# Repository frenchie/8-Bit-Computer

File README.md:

# An 8-bit Computer

My take on breadboard computer designs from [Ben Eater](https://eater.net/8bit) ([YouTube](https://www.youtube.com/channel/UCS0N5baNlQWJCUrhCEo8WlA)) and [James Bates](https://github.com/jamesbates/jcpu) ([YouTube](https://www.youtube.com/channel/UCH09NwwJsfThwLKvc6kxl4Q)).

## Licensing

* The AVR Code for the 7-segment display driver, ALU & Clock are available to use under a MIT license
* The Microcode generator & associated tools are available to use under a MIT license
* All KiCAD design files are licensed Creative Commons Attribution-ShareAlike 4.0 International (CC BY-SA 4.0)
* The AVR In-System Programmer AVR includes Peter Fluery's i2c library and is licensed under the GPLv3
* The Included AVR Makefiles are Public Domain.

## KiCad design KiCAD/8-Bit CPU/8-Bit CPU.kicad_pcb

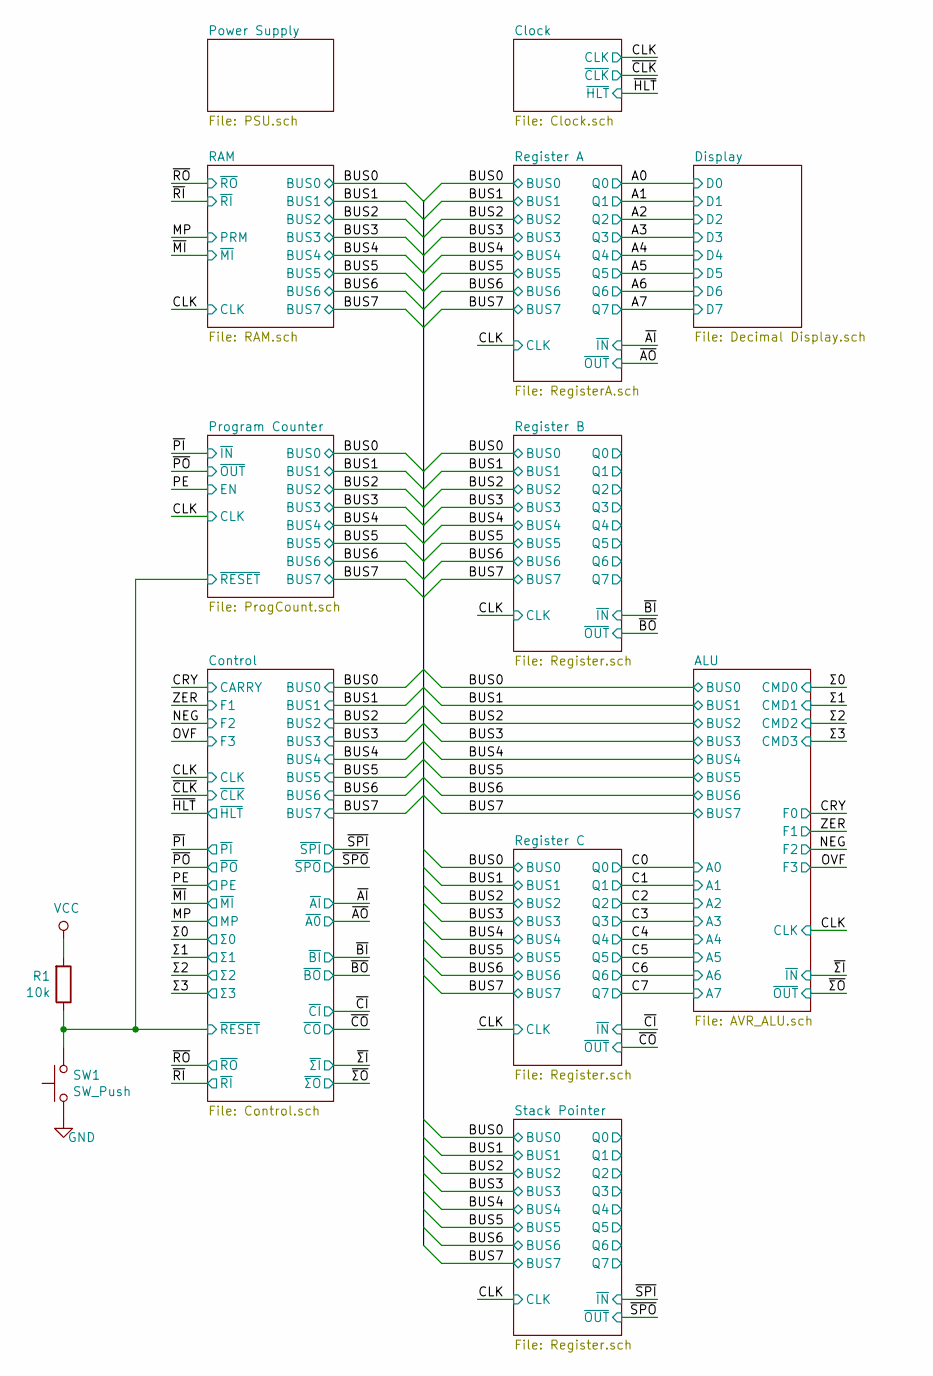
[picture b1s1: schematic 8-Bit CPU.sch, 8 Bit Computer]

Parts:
R1: 10k; R_0805_2012Metric
SW1: SW_Push; SW_TH_Tactile_Omron_B3F-10xx_Fixed

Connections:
/Control/~RESET: R1.1, SW1.2; also elsewhere on the board
GND: SW1.1; also elsewhere on the board
VCC: R1.2; also elsewhere on the board

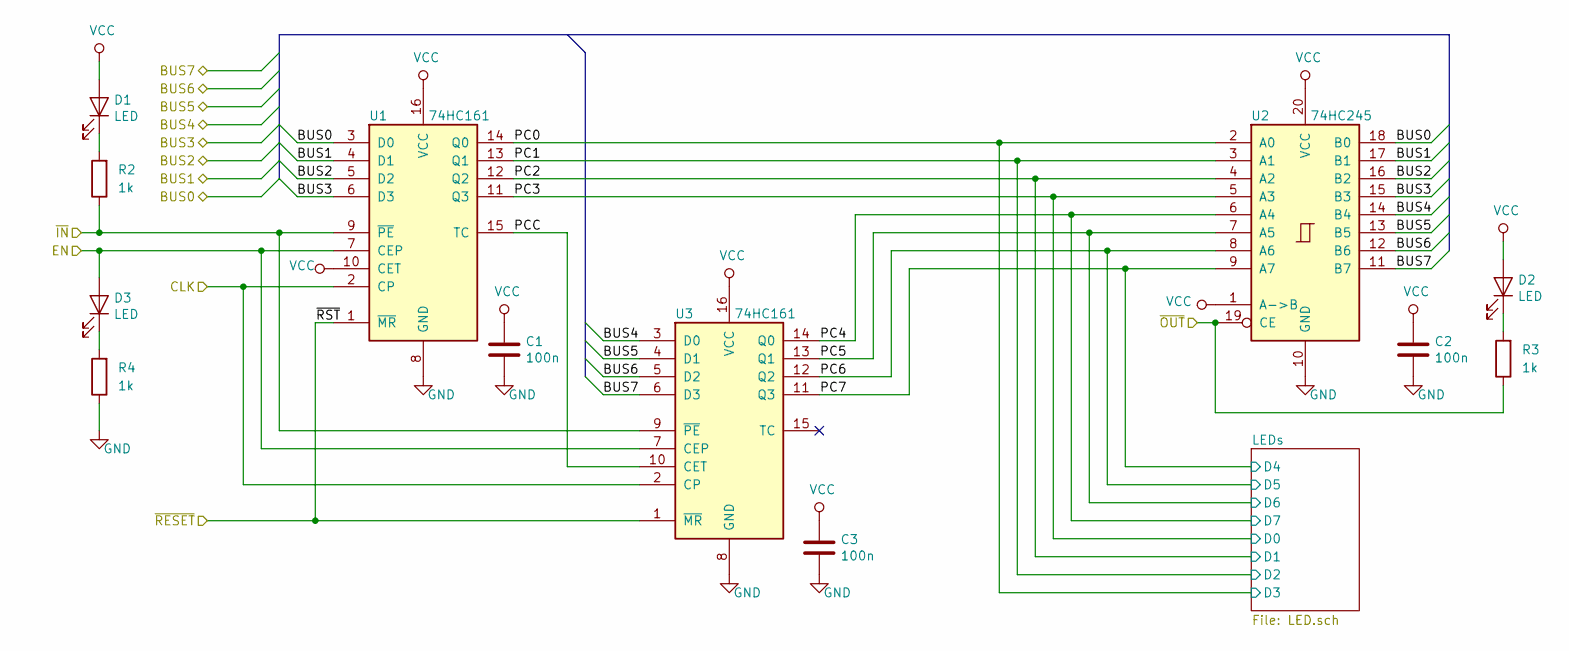
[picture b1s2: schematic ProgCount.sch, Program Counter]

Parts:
C1, C2, C3: 100n; C_0805_2012Metric
D1, D2, D3: LED; LED_0805_2012Metric
R2, R3, R4: 1k; R_0805_2012Metric
U1, U3: 74HC161; SOIC-16_3.9x9.9mm_P1.27mm
U2: 74HC245; SOIC-20W_7.5x12.8mm_P1.27mm_Rounded

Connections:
/BUS0: U1.3 (D0), U2.18 (B0); also elsewhere on the board
/BUS1: U1.4 (D1), U2.17 (B1); also elsewhere on the board
/BUS2: U1.5 (D2), U2.16 (B2); also elsewhere on the board
/BUS3: U1.6 (D3), U2.15 (B3); also elsewhere on the board
/BUS4: U2.14 (B4), U3.3 (D0); also elsewhere on the board
/BUS5: U2.13 (B5), U3.4 (D1); also elsewhere on the board
/BUS6: U2.12 (B6), U3.5 (D2); also elsewhere on the board
/BUS7: U2.11 (B7), U3.6 (D3); also elsewhere on the board
/CLK: U1.2 (CP), U3.2 (CP); also elsewhere on the board
/Control/~RESET: U1.1 (~MR), U3.1 (~MR); also elsewhere on the board
/PE: D3.2 (A), U1.7 (CEP), U3.7 (CEP); also elsewhere on the board
/Program Counter/PC0: U1.14 (Q0), U2.2 (A0); also elsewhere on the board
/Program Counter/PC1: U1.13 (Q1), U2.3 (A1); also elsewhere on the board
/Program Counter/PC2: U1.12 (Q2), U2.4 (A2); also elsewhere on the board
/Program Counter/PC3: U1.11 (Q3), U2.5 (A3); also elsewhere on the board
/Program Counter/PC4: U2.6 (A4), U3.14 (Q0); also elsewhere on the board
/Program Counter/PC5: U2.7 (A5), U3.13 (Q1); also elsewhere on the board
/Program Counter/PC6: U2.8 (A6), U3.12 (Q2); also elsewhere on the board
/Program Counter/PC7: U2.9 (A7), U3.11 (Q3); also elsewhere on the board
/Program Counter/PCC: U1.15 (TC), U3.10 (CET)
/~PI: R2.1, U1.9 (~PE), U3.9 (~PE); also elsewhere on the board
/~PO: R3.1, U2.19 (CE); also elsewhere on the board
GND: C1.2, C2.2, C3.2, R4.1, U1.8 (GND), U2.10 (GND), U3.8 (GND); also elsewhere on the board
unnamed: D1.1 (K), R2.2
unnamed: D2.1 (K), R3.2
unnamed: D3.1 (K), R4.2
VCC: C1.1, C2.1, C3.1, D1.2 (A), D2.2 (A), U1.10 (CET), U1.16 (VCC), U2.1 (A->B), U2.20 (VCC), U3.16 (VCC); also elsewhere on the board

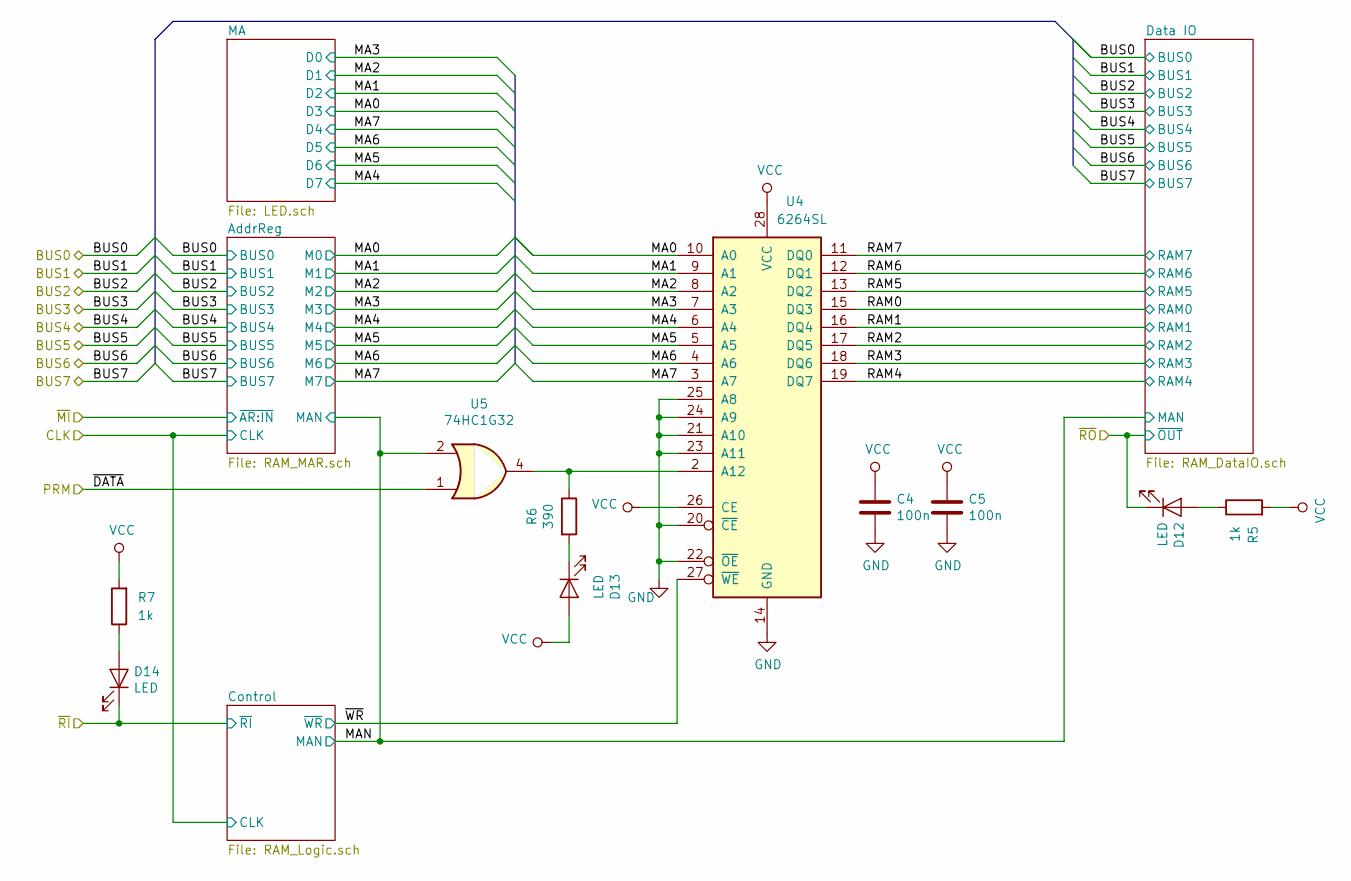
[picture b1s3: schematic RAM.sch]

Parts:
C4, C5: 100n; C_0805_2012Metric
D12, D13, D14: LED; LED_0805_2012Metric
R5, R7: 1k; R_0805_2012Metric
R6: 390; R_0805_2012Metric
U4: 6264SL; SOIC-28W-LY6264
U5: 74HC1G32; TSOP-5_1.65x3.05mm_P0.95mm

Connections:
/MP: U5.1; also elsewhere on the board
/RAM/MA0: U4.10 (A0); also elsewhere on the board
/RAM/MA1: U4.9 (A1); also elsewhere on the board
/RAM/MA2: U4.8 (A2); also elsewhere on the board
/RAM/MA3: U4.7 (A3); also elsewhere on the board
/RAM/MA4: U4.6 (A4); also elsewhere on the board
/RAM/MA5: U4.5 (A5); also elsewhere on the board
/RAM/MA6: U4.4 (A6); also elsewhere on the board
/RAM/MA7: U4.3 (A7); also elsewhere on the board
/RAM/MAN: U5.2; also elsewhere on the board
/RAM/RAM0: U4.15 (DQ3); also elsewhere on the board
/RAM/RAM1: U4.16 (DQ4); also elsewhere on the board
/RAM/RAM2: U4.17 (DQ5); also elsewhere on the board
/RAM/RAM3: U4.18 (DQ6); also elsewhere on the board
/RAM/RAM4: U4.19 (DQ7); also elsewhere on the board
/RAM/RAM5: U4.13 (DQ2); also elsewhere on the board
/RAM/RAM6: U4.12 (DQ1); also elsewhere on the board
/RAM/RAM7: U4.11 (DQ0); also elsewhere on the board
/RAM/~WR: U4.27 (~WE); also elsewhere on the board
/~RI: D14.1 (K); also elsewhere on the board
/~RO: D12.1 (K); also elsewhere on the board
GND: C4.2, C5.2, U4.14 (GND), U4.20 (~CE), U4.21 (A10), U4.22 (~OE), U4.23 (A11), U4.24 (A9), U4.25 (A8), U5.3 (GND); also elsewhere on the board
unnamed: D12.2 (A), R5.1
unnamed: D13.1 (K), R6.2
unnamed: D14.2 (A), R7.1
unnamed: R6.1, U4.2 (A12), U5.4
VCC: C4.1, C5.1, D13.2 (A), R5.2, R7.2, U4.26 (CE), U4.28 (VCC), U5.5 (VCC); also elsewhere on the board

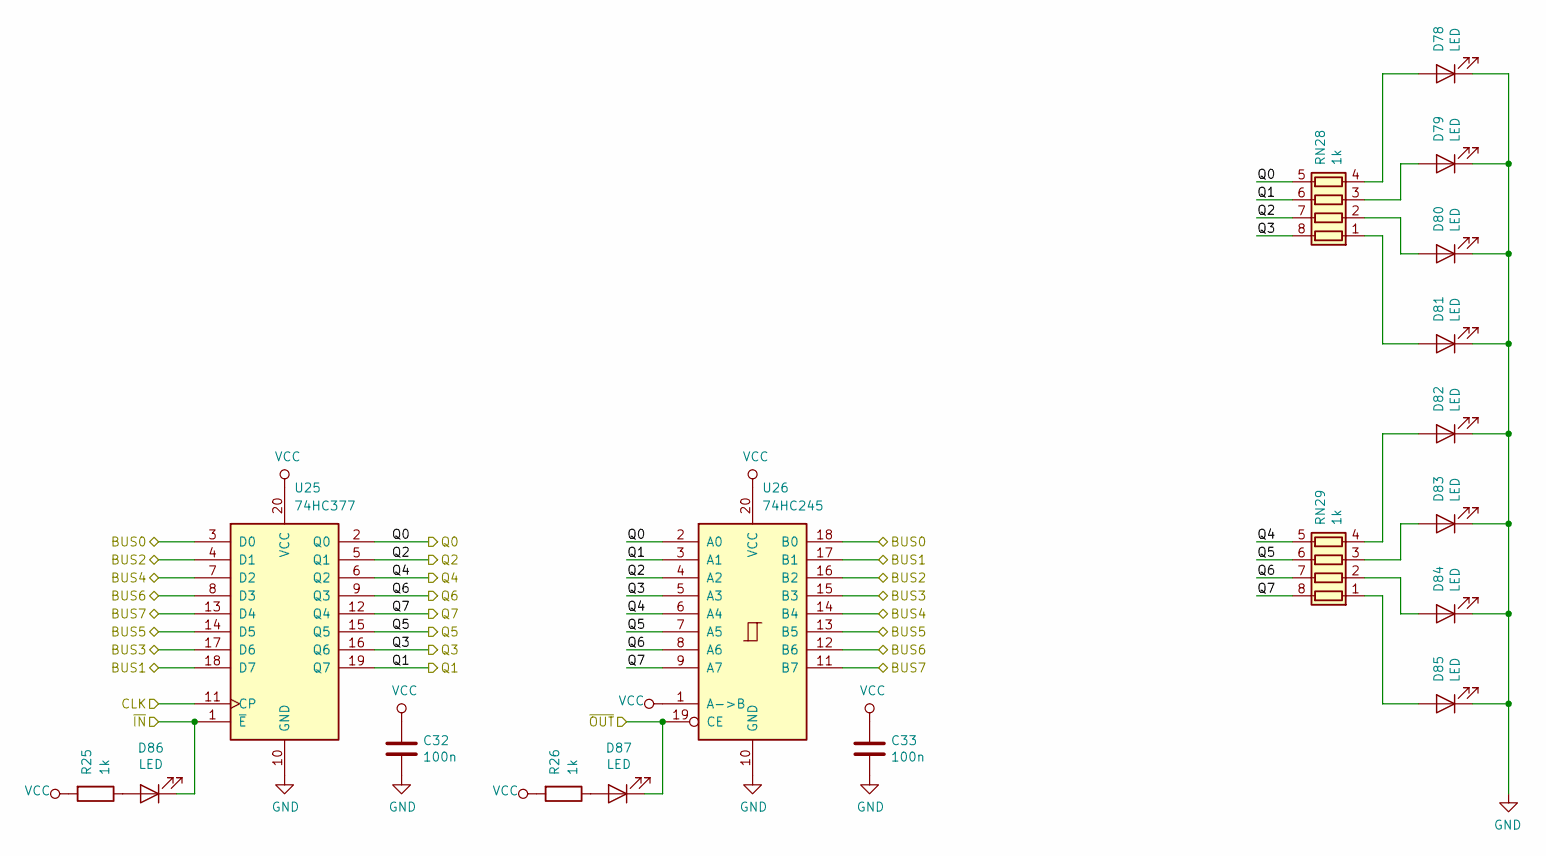
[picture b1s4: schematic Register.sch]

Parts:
C32, C33: 100n; C_0805_2012Metric
D78, D79, D80, D81, D82, D83, D84, D85, D86, D87: LED; LED_0805_2012Metric
R25, R26: 1k; R_0805_2012Metric
RN28, RN29: 1k; R_Array_Concave_4x0603
U25: 74HC377; SOIC-20W_7.5x12.8mm_P1.27mm_Rounded
U26: 74HC245; SOIC-20W_7.5x12.8mm_P1.27mm_Rounded

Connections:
/BUS0: U25.3 (D0), U26.18 (B0); also elsewhere on the board
/BUS1: U25.18 (D7), U26.17 (B1); also elsewhere on the board
/BUS2: U25.4 (D1), U26.16 (B2); also elsewhere on the board
/BUS3: U25.17 (D6), U26.15 (B3); also elsewhere on the board
/BUS4: U25.7 (D2), U26.14 (B4); also elsewhere on the board
/BUS5: U25.14 (D5), U26.13 (B5); also elsewhere on the board
/BUS6: U25.8 (D3), U26.12 (B6); also elsewhere on the board
/BUS7: U25.13 (D4), U26.11 (B7); also elsewhere on the board
/CLK: U25.11 (CP); also elsewhere on the board
/Stack Pointer/Q0: RN28.5 (R4.2), U25.2 (Q0), U26.2 (A0)
/Stack Pointer/Q1: RN28.6 (R3.2), U25.19 (Q7), U26.3 (A1)
/Stack Pointer/Q2: RN28.7 (R2.2), U25.5 (Q1), U26.4 (A2)
/Stack Pointer/Q3: RN28.8 (R1.2), U25.16 (Q6), U26.5 (A3)
/Stack Pointer/Q4: RN29.5 (R4.2), U25.6 (Q2), U26.6 (A4)
/Stack Pointer/Q5: RN29.6 (R3.2), U25.15 (Q5), U26.7 (A5)
/Stack Pointer/Q6: RN29.7 (R2.2), U25.9 (Q3), U26.8 (A6)
/Stack Pointer/Q7: RN29.8 (R1.2), U25.12 (Q4), U26.9 (A7)
/~SPI: D86.1 (K), U25.1 (~E); also elsewhere on the board
/~SPO: D87.1 (K), U26.19 (CE); also elsewhere on the board
GND: C32.2, C33.2, D78.1 (K), D79.1 (K), D80.1 (K), D81.1 (K), D82.1 (K), D83.1 (K), D84.1 (K), D85.1 (K), U25.10 (GND), U26.10 (GND); also elsewhere on the board
unnamed: D78.2 (A), RN28.4 (R4.1)
unnamed: D79.2 (A), RN28.3 (R3.1)
unnamed: D80.2 (A), RN28.2 (R2.1)
unnamed: D81.2 (A), RN28.1 (R1.1)
unnamed: D82.2 (A), RN29.4 (R4.1)
unnamed: D83.2 (A), RN29.3 (R3.1)
unnamed: D84.2 (A), RN29.2 (R2.1)
unnamed: D85.2 (A), RN29.1 (R1.1)
unnamed: D86.2 (A), R25.1
unnamed: D87.2 (A), R26.1
VCC: C32.1, C33.1, R25.2, R26.2, U25.20 (VCC), U26.1 (A->B), U26.20 (VCC); also elsewhere on the board

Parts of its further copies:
C17, C18, C30, C31: 100n; C_0805_2012Metric
D34, D35, D36, D37, D38, D39, D40, D41, D42, D43, D68, D69, D70, D71, D72, D73, D74, D75, D76, D77: LED; LED_0805_2012Metric
R16, R17, R23, R24: 1k; R_0805_2012Metric
RN15, RN16, RN26, RN27: 1k; R_Array_Concave_4x0603
U14, U23: 74HC377; SOIC-20W_7.5x12.8mm_P1.27mm_Rounded
U15, U24: 74HC245; SOIC-20W_7.5x12.8mm_P1.27mm_Rounded

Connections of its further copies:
/BUS0: U14.3 (D0), U15.18 (B0), U23.3 (D0), U24.18 (B0); also elsewhere on the board
/BUS1: U14.18 (D7), U15.17 (B1), U23.18 (D7), U24.17 (B1); also elsewhere on the board
/BUS2: U14.4 (D1), U15.16 (B2), U23.4 (D1), U24.16 (B2); also elsewhere on the board
/BUS3: U14.17 (D6), U15.15 (B3), U23.17 (D6), U24.15 (B3); also elsewhere on the board
/BUS4: U14.7 (D2), U15.14 (B4), U23.7 (D2), U24.14 (B4); also elsewhere on the board
/BUS5: U14.14 (D5), U15.13 (B5), U23.14 (D5), U24.13 (B5); also elsewhere on the board
/BUS6: U14.8 (D3), U15.12 (B6), U23.8 (D3), U24.12 (B6); also elsewhere on the board
/BUS7: U14.13 (D4), U15.11 (B7), U23.13 (D4), U24.11 (B7); also elsewhere on the board
/C0: RN26.5 (R4.2), U23.2 (Q0), U24.2 (A0); also elsewhere on the board
/C1: RN26.6 (R3.2), U23.19 (Q7), U24.3 (A1); also elsewhere on the board
/C2: RN26.7 (R2.2), U23.5 (Q1), U24.4 (A2); also elsewhere on the board
/C3: RN26.8 (R1.2), U23.16 (Q6), U24.5 (A3); also elsewhere on the board
/C4: RN27.5 (R4.2), U23.6 (Q2), U24.6 (A4); also elsewhere on the board
/C5: RN27.6 (R3.2), U23.15 (Q5), U24.7 (A5); also elsewhere on the board
/C6: RN27.7 (R2.2), U23.9 (Q3), U24.8 (A6); also elsewhere on the board
/C7: RN27.8 (R1.2), U23.12 (Q4), U24.9 (A7); also elsewhere on the board
/CLK: U14.11 (CP), U23.11 (CP); also elsewhere on the board
/Register B/Q0: RN15.5 (R4.2), U14.2 (Q0), U15.2 (A0)
/Register B/Q1: RN15.6 (R3.2), U14.19 (Q7), U15.3 (A1)
/Register B/Q2: RN15.7 (R2.2), U14.5 (Q1), U15.4 (A2)
/Register B/Q3: RN15.8 (R1.2), U14.16 (Q6), U15.5 (A3)
/Register B/Q4: RN16.5 (R4.2), U14.6 (Q2), U15.6 (A4)
/Register B/Q5: RN16.6 (R3.2), U14.15 (Q5), U15.7 (A5)
/Register B/Q6: RN16.7 (R2.2), U14.9 (Q3), U15.8 (A6)
/Register B/Q7: RN16.8 (R1.2), U14.12 (Q4), U15.9 (A7)
/~BI: D42.1 (K), U14.1 (~E); also elsewhere on the board
/~BO: D43.1 (K), U15.19 (CE); also elsewhere on the board
/~CI: D76.1 (K), U23.1 (~E); also elsewhere on the board
/~CO: D77.1 (K), U24.19 (CE); also elsewhere on the board
GND: C17.2, C18.2, C30.2, C31.2, D34.1 (K), D35.1 (K), D36.1 (K), D37.1 (K), D38.1 (K), D39.1 (K), D40.1 (K), D41.1 (K), D68.1 (K), D69.1 (K), D70.1 (K), D71.1 (K), D72.1 (K), D73.1 (K), D74.1 (K), D75.1 (K), U14.10 (GND), U15.10 (GND), U23.10 (GND), U24.10 (GND); also elsewhere on the board
unnamed: D34.2 (A), RN15.4 (R4.1)
unnamed: D35.2 (A), RN15.3 (R3.1)
unnamed: D36.2 (A), RN15.2 (R2.1)
unnamed: D37.2 (A), RN15.1 (R1.1)
unnamed: D38.2 (A), RN16.4 (R4.1)
unnamed: D39.2 (A), RN16.3 (R3.1)
unnamed: D40.2 (A), RN16.2 (R2.1)
unnamed: D41.2 (A), RN16.1 (R1.1)
unnamed: D42.2 (A), R16.1
unnamed: D43.2 (A), R17.1
unnamed: D68.2 (A), RN26.4 (R4.1)
unnamed: D69.2 (A), RN26.3 (R3.1)
unnamed: D70.2 (A), RN26.2 (R2.1)
unnamed: D71.2 (A), RN26.1 (R1.1)
unnamed: D72.2 (A), RN27.4 (R4.1)
unnamed: D73.2 (A), RN27.3 (R3.1)
unnamed: D74.2 (A), RN27.2 (R2.1)
unnamed: D75.2 (A), RN27.1 (R1.1)
unnamed: D76.2 (A), R23.1
unnamed: D77.2 (A), R24.1
VCC: C17.1, C18.1, C30.1, C31.1, R16.2, R17.2, R23.2, R24.2, U14.20 (VCC), U15.1 (A->B), U15.20 (VCC), U23.20 (VCC), U24.1 (A->B), U24.20 (VCC); also elsewhere on the board

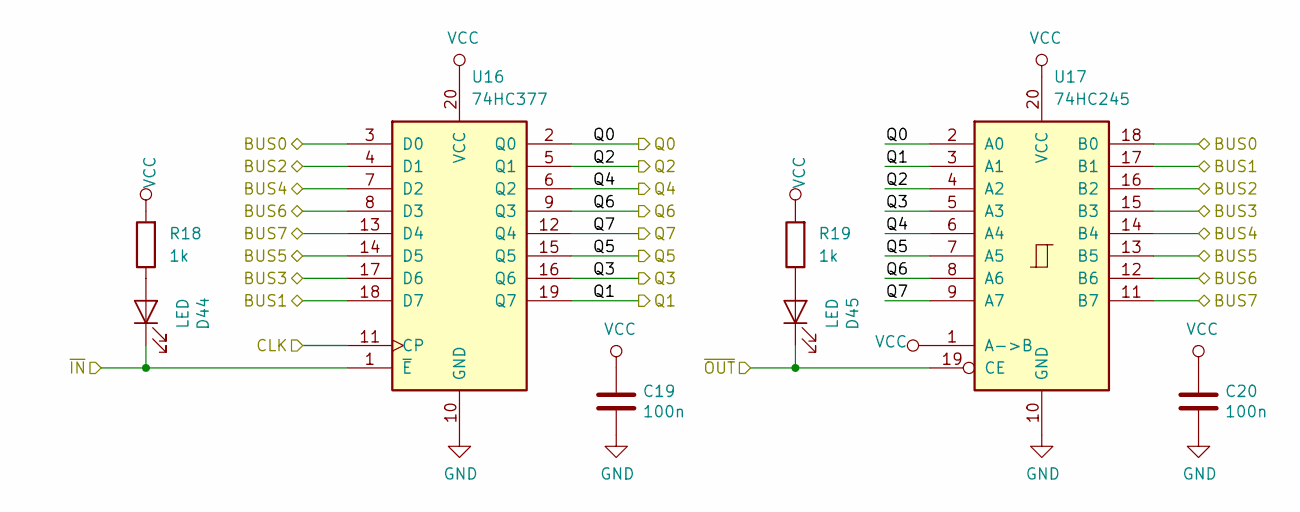
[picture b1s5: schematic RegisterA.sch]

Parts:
C19, C20: 100n; C_0805_2012Metric
D44, D45: LED; LED_0805_2012Metric
R18, R19: 1k; R_0805_2012Metric
U16: 74HC377; SOIC-20W_7.5x12.8mm_P1.27mm_Rounded
U17: 74HC245; SOIC-20W_7.5x12.8mm_P1.27mm_Rounded

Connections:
/A0: U16.2 (Q0), U17.2 (A0); also elsewhere on the board
/A1: U16.19 (Q7), U17.3 (A1); also elsewhere on the board
/A2: U16.5 (Q1), U17.4 (A2); also elsewhere on the board
/A3: U16.16 (Q6), U17.5 (A3); also elsewhere on the board
/A4: U16.6 (Q2), U17.6 (A4); also elsewhere on the board
/A5: U16.15 (Q5), U17.7 (A5); also elsewhere on the board
/A6: U16.9 (Q3), U17.8 (A6); also elsewhere on the board
/A7: U16.12 (Q4), U17.9 (A7); also elsewhere on the board
/BUS0: U16.3 (D0), U17.18 (B0); also elsewhere on the board
/BUS1: U16.18 (D7), U17.17 (B1); also elsewhere on the board
/BUS2: U16.4 (D1), U17.16 (B2); also elsewhere on the board
/BUS3: U16.17 (D6), U17.15 (B3); also elsewhere on the board
/BUS4: U16.7 (D2), U17.14 (B4); also elsewhere on the board
/BUS5: U16.14 (D5), U17.13 (B5); also elsewhere on the board
/BUS6: U16.8 (D3), U17.12 (B6); also elsewhere on the board
/BUS7: U16.13 (D4), U17.11 (B7); also elsewhere on the board
/CLK: U16.11 (CP); also elsewhere on the board
/~AI: D44.1 (K), U16.1 (~E); also elsewhere on the board
/~AO: D45.1 (K), U17.19 (CE); also elsewhere on the board
GND: C19.2, C20.2, U16.10 (GND), U17.10 (GND); also elsewhere on the board
unnamed: D44.2 (A), R18.1
unnamed: D45.2 (A), R19.1
VCC: C19.1, C20.1, R18.2, R19.2, U16.20 (VCC), U17.1 (A->B), U17.20 (VCC); also elsewhere on the board

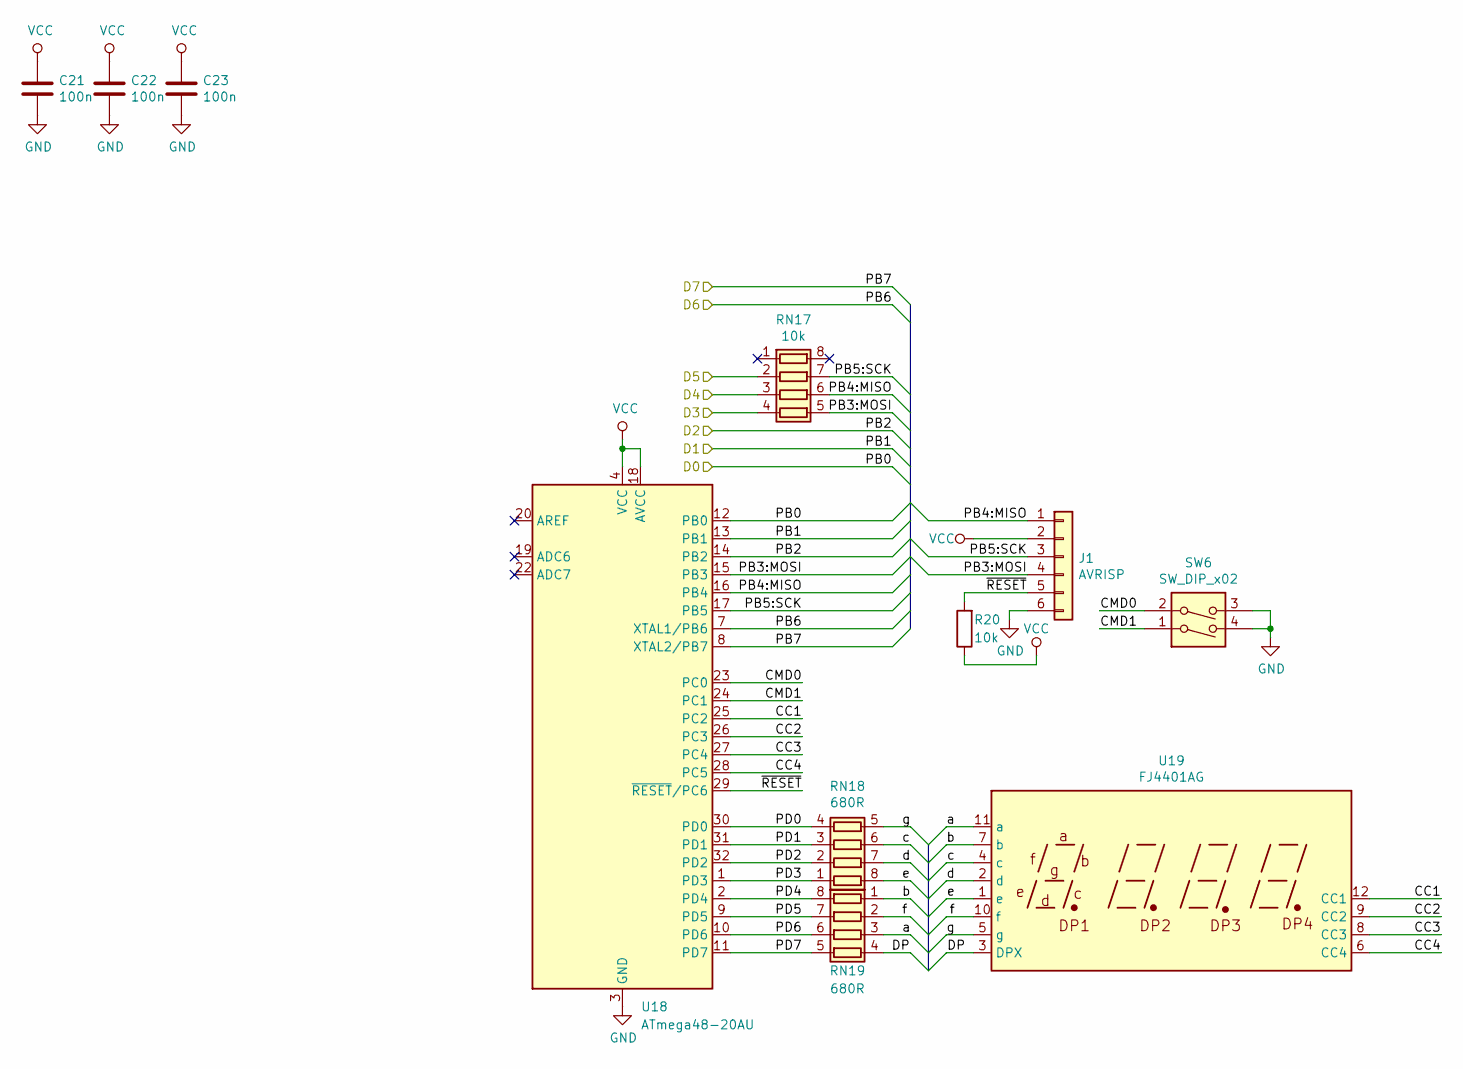
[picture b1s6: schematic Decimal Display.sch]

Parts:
C21, C22, C23: 100n; C_0805_2012Metric
J1: AVRISP; PinHeader_2x03_P2.54mm_Vertical
R20: 10k; R_0805_2012Metric
RN17: 10k; R_Array_Concave_4x0603
RN18, RN19: 680R; R_Array_Concave_4x0603
SW6: SW_DIP_x02; SW_DIP_SPSTx02_Slide_9.78x7.26mm_W7.62mm_P2.54mm
U18: ATmega48-20AU; TQFP-32_7x7mm_P0.8mm
U19: FJ4401AG

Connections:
/A0: U18.12 (PB0); also elsewhere on the board
/A1: U18.13 (PB1); also elsewhere on the board
/A2: U18.14 (PB2); also elsewhere on the board
/A3: RN17.4 (R4.1); also elsewhere on the board
/A4: RN17.3 (R3.1); also elsewhere on the board
/A5: RN17.2 (R2.1); also elsewhere on the board
/A6: U18.7 (XTAL1/PB6); also elsewhere on the board
/A7: U18.8 (XTAL2/PB7); also elsewhere on the board
/Display/CC1: U18.25 (PC2), U19.12 (CC1)
/Display/CC2: U18.26 (PC3), U19.9 (CC2)
/Display/CC3: U18.27 (PC4), U19.8 (CC3)
/Display/CC4: U18.28 (PC5), U19.6 (CC4)
/Display/CMD0: SW6.2, U18.23 (PC0)
/Display/CMD1: SW6.1, U18.24 (PC1)
/Display/DP: RN19.4 (R4.1), U19.3 (DPX)
/Display/PB3:MOSI: J1.4, RN17.5 (R4.2), U18.15 (PB3)
/Display/PB4:MISO: J1.1, RN17.6 (R3.2), U18.16 (PB4)
/Display/PB5:SCK: J1.3, RN17.7 (R2.2), U18.17 (PB5)
/Display/PD0: RN18.4 (R4.1), U18.30 (PD0)
/Display/PD1: RN18.3 (R3.1), U18.31 (PD1)
/Display/PD2: RN18.2 (R2.1), U18.32 (PD2)
/Display/PD3: RN18.1 (R1.1), U18.1 (PD3)
/Display/PD4: RN19.8 (R1.2), U18.2 (PD4)
/Display/PD5: RN19.7 (R2.2), U18.9 (PD5)
/Display/PD6: RN19.6 (R3.2), U18.10 (PD6)
/Display/PD7: RN19.5 (R4.2), U18.11 (PD7)
/Display/a: RN19.3 (R3.1), U19.11 (a)
/Display/b: RN19.1 (R1.1), U19.7 (b)
/Display/c: RN18.6 (R3.2), U19.4 (c)
/Display/d: RN18.7 (R2.2), U19.2 (d)
/Display/e: RN18.8 (R1.2), U19.1 (e)
/Display/f: RN19.2 (R2.1), U19.10 (f)
/Display/g: RN18.5 (R4.2), U19.5 (g)
/Display/~RESET: J1.5, R20.2, U18.29 (~RESET~/PC6)
GND: C21.2, C22.2, C23.2, J1.6, SW6.3, SW6.4, U18.3 (GND), U18.5 (GND), U18.21 (GND); also elsewhere on the board
VCC: C21.1, C22.1, C23.1, J1.2, R20.1, U18.4 (VCC), U18.6 (VCC), U18.18 (AVCC); also elsewhere on the board

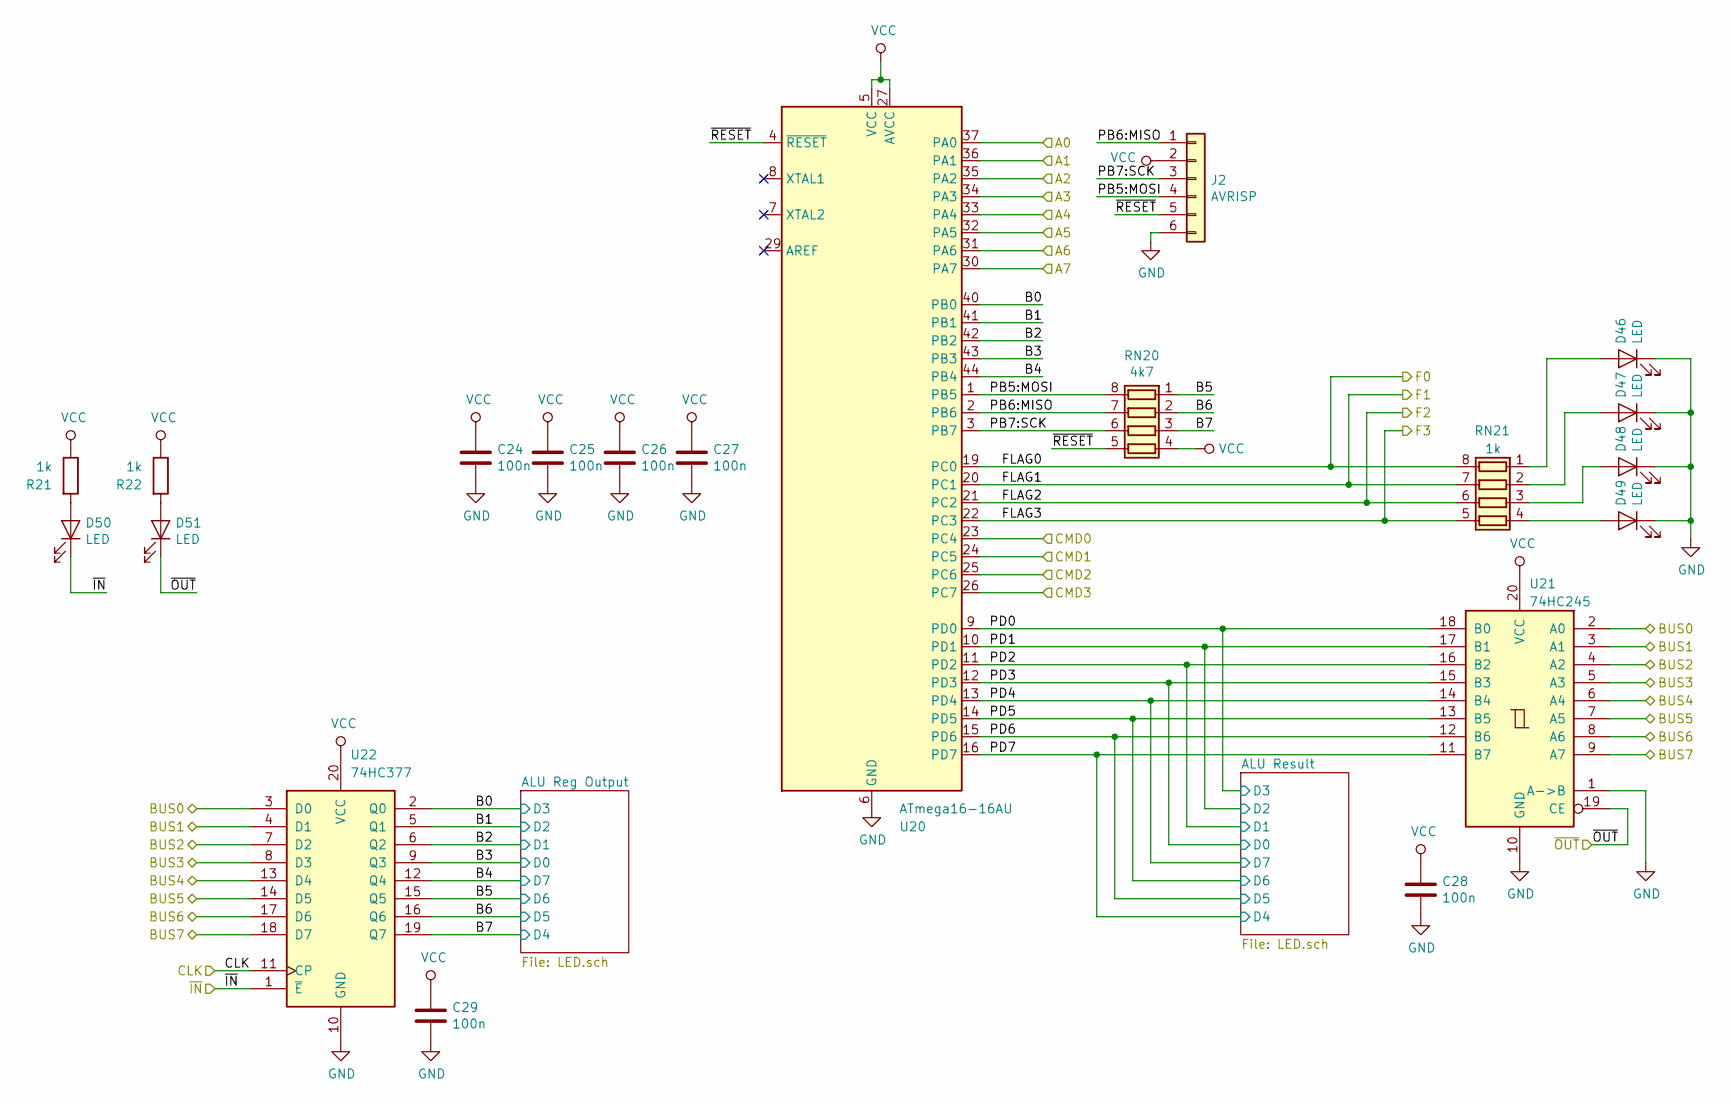
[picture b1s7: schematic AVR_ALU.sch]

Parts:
C24, C25, C26, C27, C28, C29: 100n; C_0805_2012Metric
D46, D47, D48, D49, D50, D51: LED; LED_0805_2012Metric
J2: AVRISP; PinHeader_2x03_P2.54mm_Vertical
R21, R22: 1k; R_0805_2012Metric
RN20: 4k7; R_Array_Concave_4x0603
RN21: 1k; R_Array_Concave_4x0603
U20: ATmega16-16AU; TQFP-44_10x10mm_P0.8mm
U21: 74HC245; SOIC-20W_7.5x12.8mm_P1.27mm_Rounded
U22: 74HC377; SOIC-20W_7.5x12.8mm_P1.27mm_Rounded

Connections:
/ALU/B0: U20.40 (PB0), U22.2 (Q0); also elsewhere on the board
/ALU/B1: U20.41 (PB1), U22.5 (Q1); also elsewhere on the board
/ALU/B2: U20.42 (PB2), U22.6 (Q2); also elsewhere on the board
/ALU/B3: U20.43 (PB3), U22.9 (Q3); also elsewhere on the board
/ALU/B4: U20.44 (PB4), U22.12 (Q4); also elsewhere on the board
/ALU/B5: RN20.1 (R1.1), U22.15 (Q5); also elsewhere on the board
/ALU/B6: RN20.2 (R2.1), U22.16 (Q6); also elsewhere on the board
/ALU/B7: RN20.3 (R3.1), U22.19 (Q7); also elsewhere on the board
/ALU/PB5:MOSI: J2.4, RN20.8 (R1.2), U20.1 (PB5)
/ALU/PB6:MISO: J2.1, RN20.7 (R2.2), U20.2 (PB6)
/ALU/PB7:SCK: J2.3, RN20.6 (R3.2), U20.3 (PB7)
/ALU/PD0: U20.9 (PD0), U21.18 (B0); also elsewhere on the board
/ALU/PD1: U20.10 (PD1), U21.17 (B1); also elsewhere on the board
/ALU/PD2: U20.11 (PD2), U21.16 (B2); also elsewhere on the board
/ALU/PD3: U20.12 (PD3), U21.15 (B3); also elsewhere on the board
/ALU/PD4: U20.13 (PD4), U21.14 (B4); also elsewhere on the board
/ALU/PD5: U20.14 (PD5), U21.13 (B5); also elsewhere on the board
/ALU/PD6: U20.15 (PD6), U21.12 (B6); also elsewhere on the board
/ALU/PD7: U20.16 (PD7), U21.11 (B7); also elsewhere on the board
/ALU/~RESET: J2.5, RN20.5 (R4.2), U20.4 (~RESET)
/BUS0: U21.2 (A0), U22.3 (D0); also elsewhere on the board
/BUS1: U21.3 (A1), U22.4 (D1); also elsewhere on the board
/BUS2: U21.4 (A2), U22.7 (D2); also elsewhere on the board
/BUS3: U21.5 (A3), U22.8 (D3); also elsewhere on the board
/BUS4: U21.6 (A4), U22.13 (D4); also elsewhere on the board
/BUS5: U21.7 (A5), U22.14 (D5); also elsewhere on the board
/BUS6: U21.8 (A6), U22.17 (D6); also elsewhere on the board
/BUS7: U21.9 (A7), U22.18 (D7); also elsewhere on the board
/C0: U20.37 (PA0); also elsewhere on the board
/C1: U20.36 (PA1); also elsewhere on the board
/C2: U20.35 (PA2); also elsewhere on the board
/C3: U20.34 (PA3); also elsewhere on the board
/C4: U20.33 (PA4); also elsewhere on the board
/C5: U20.32 (PA5); also elsewhere on the board
/C6: U20.31 (PA6); also elsewhere on the board
/C7: U20.30 (PA7); also elsewhere on the board
/CLK: U22.11 (CP); also elsewhere on the board
/CRY: RN21.8 (R1.2), U20.19 (PC0); also elsewhere on the board
/NEG: RN21.6 (R3.2), U20.21 (PC2); also elsewhere on the board
/OVF: RN21.5 (R4.2), U20.22 (PC3); also elsewhere on the board
/ZER: RN21.7 (R2.2), U20.20 (PC1); also elsewhere on the board
/~ΣI: D50.1 (K), U22.1 (~E); also elsewhere on the board
/~ΣO: D51.1 (K), U21.19 (CE); also elsewhere on the board
/Σ0: U20.23 (PC4); also elsewhere on the board
/Σ1: U20.24 (PC5); also elsewhere on the board
/Σ2: U20.25 (PC6); also elsewhere on the board
/Σ3: U20.26 (PC7); also elsewhere on the board
GND: C24.2, C25.2, C26.2, C27.2, C28.2, C29.2, D46.1 (K), D47.1 (K), D48.1 (K), D49.1 (K), J2.6, U20.6 (GND), U20.18 (GND), U20.28 (GND), U20.39 (GND), U21.1 (A->B), U21.10 (GND), U22.10 (GND); also elsewhere on the board
unnamed: D46.2 (A), RN21.1 (R1.1)
unnamed: D47.2 (A), RN21.2 (R2.1)
unnamed: D48.2 (A), RN21.3 (R3.1)
unnamed: D49.2 (A), RN21.4 (R4.1)
unnamed: D50.2 (A), R21.2
unnamed: D51.2 (A), R22.2
VCC: C24.1, C25.1, C26.1, C27.1, C28.1, C29.1, J2.2, R21.1, R22.1, RN20.4 (R4.1), U20.5 (VCC), U20.17 (VCC), U20.27 (AVCC), U20.38 (VCC), U21.20 (VCC), U22.20 (VCC); also elsewhere on the board

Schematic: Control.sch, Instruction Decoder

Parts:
C34, C35, C36: 100n; C_0805_2012Metric
U27: 74HC08; SOIC-14_3.9x8.7mm_P1.27mm_JCF
U28, U29: 74HC1G32; TSOP-5_1.65x3.05mm_P0.95mm

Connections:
/Control/A0: U27.13; also elsewhere on the board
/Control/A1: U27.5; also elsewhere on the board
/Control/A2: U27.10; also elsewhere on the board
/Control/FL: U29.4; also elsewhere on the board
/NEG: U27.4; also elsewhere on the board
/OVF: U27.9; also elsewhere on the board
/ZER: U27.12; also elsewhere on the board
GND: C34.2, C35.2, C36.2, U27.1, U27.2, U27.7, U28.3 (GND), U29.3 (GND); also elsewhere on the board
unnamed: U27.6, U28.1
unnamed: U27.8, U28.2
unnamed: U27.11, U29.1
unnamed: U28.4, U29.2
VCC: C34.1, C35.1, C36.1, U27.14, U28.5 (VCC), U29.5 (VCC); also elsewhere on the board

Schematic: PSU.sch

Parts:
C55: 100u; C_Elec_6.3x7.7
C56: 10u; C_1206_3216Metric
C57: 22u; C_1206_3216Metric
J5: 7-20V; PJ-202A
U48: K7805M-1000R3; K78xxM-1000R3

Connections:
+12V: C55.1, C56.1, J5.1, U48.1 (IN)
GND: C55.2, C56.2, C57.2, J5.2, J5.3, U48.2 (GND); also elsewhere on the board
VCC: C57.1, U48.3 (OUT); also elsewhere on the board

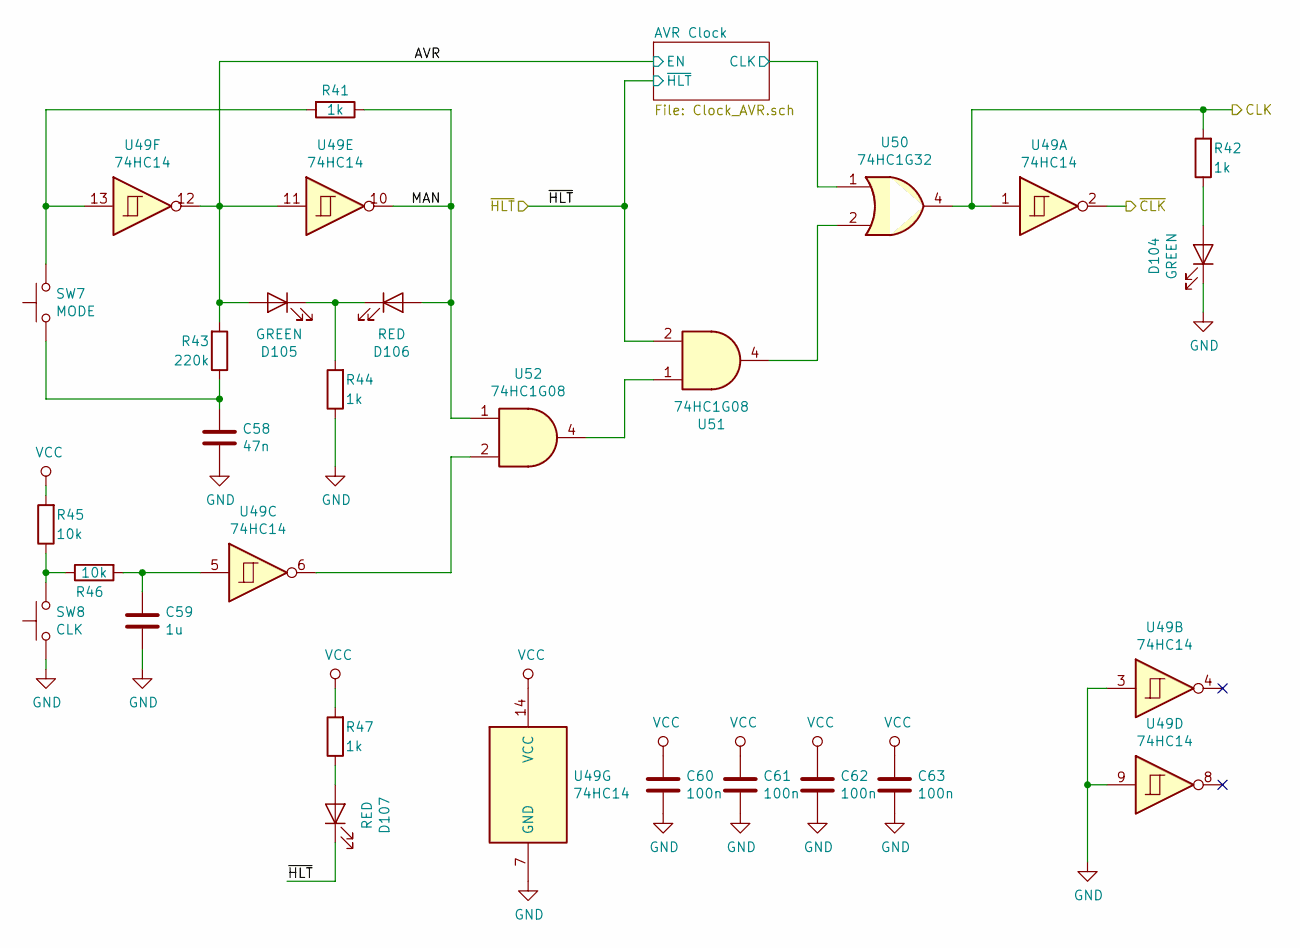
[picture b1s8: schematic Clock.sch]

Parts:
C58: 47n; C_0805_2012Metric
C59: 1u; C_0805_2012Metric
C60, C61, C62, C63: 100n; C_0805_2012Metric
D104, D105: GREEN; LED_0805_2012Metric
D106, D107: RED; LED_0805_2012Metric
R41, R42, R44, R47: 1k; R_0805_2012Metric
R43: 220k; R_0805_2012Metric
R45, R46: 10k; R_0805_2012Metric
SW7: MODE; SW_TH_Tactile_Omron_B3F-10xx_Fixed
SW8: CLK; SW_TH_Tactile_Omron_B3F-10xx_Fixed
U49: 74HC14; SOIC-14_3.9x8.7mm_P1.27mm_JCF
U50: 74HC1G32; TSOP-5_1.65x3.05mm_P0.95mm
U51, U52: 74HC1G08; TSOP-5_1.65x3.05mm_P0.95mm

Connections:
/CLK: R42.2, U49.1, U50.4; also elsewhere on the board
/Clock/AVR: D105.2 (A), R43.2, U49.11, U49.12; also elsewhere on the board
/Clock/AVR Clock/CLK: U50.1; also elsewhere on the board
/Clock/MAN: D106.2 (A), R41.1, U49.10, U52.1
/~CLK: U49.2; also elsewhere on the board
/~HLT: D107.1 (K), U51.2; also elsewhere on the board
GND: C58.2, C59.2, C60.2, C61.2, C62.2, C63.2, D104.1 (K), R44.1, SW8.1, U49.3, U49.7 (GND), U49.9, U50.3 (GND), U51.3 (GND), U52.3 (GND); also elsewhere on the board
unnamed: C58.1, R43.1, SW7.1
unnamed: C59.1, R46.2, U49.5
unnamed: D104.2 (A), R42.1
unnamed: D105.1 (K), D106.1 (K), R44.2
unnamed: D107.2 (A), R47.1
unnamed: R41.2, SW7.2, U49.13
unnamed: R45.1, R46.1, SW8.2
unnamed: U49.6, U52.2
unnamed: U50.2, U51.4
unnamed: U51.1, U52.4
VCC: C60.1, C61.1, C62.1, C63.1, R45.2, R47.2, U49.14 (VCC), U50.5 (VCC), U51.5 (VCC), U52.5 (VCC); also elsewhere on the board
